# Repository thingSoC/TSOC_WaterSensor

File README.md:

# TSOC_WaterSensor - Passive Water Sensor Module :

The TSOC_WaterSensor is a simple passive water sensor with Grove Connectors, 
in an Embedded Module format for the new thingSoC, Internet of Things open standard.
It includes a secondl breakout connector for an additional sensor (Temperature/Humidity) or actuator (Relay/Mosfet).
It is designed to be used as a basement/sump water detector that engages a pump or alarm when water is present.
The addiitional connector can be used to add a humidity/temperature sensor (ie. basement too hot or too moist),
or for a an actuator, like a Relay (to turn on the sump pump when water is detected, etc.).

The TSOC_WaterSensor is a low cost, embeddable module featuring :

* Simple, Passive Water Sensor
* Additional Breakout connector
* Mounting holes
* [thingSoC Compliant Module](http://www.thingsoc.com)
* [Mikrobus Compatible Module](http://www.mikroe.com/mikrobus/) 

[TSOC_WaterSensor](https://github.com/thingSoC/TSOC_WaterSensor)

**thingSoC Reference Designs** are example thingSoC implementations that implement
various reference and testing circuits for demonstrating the use of the thingSoC libraries.
These reference designs can serve as starting templates for user designs.

---------------------------------------

## TSOC_WaterSensor Instructions

The TSOC_WaterSensor can use either digital or analog inputs for water detection.
The additional breakout connector can be used for an additional sensor (Temperature/Humidity) or actuator (Relay/Mosfet).

---------------------------------------

## TSOC_WaterSensor Status <a name="TSOC_WaterSensor_status"/>

**11/06/2016:** 
Revision 1.0 - Initial Layout released to OSHpark

---------------------------------------
## TSOC_WaterSensor Model Images

[TSOC_WaterSensor](https://github.com/thingSoC/TSOC_WaterSensor)

[TSOC_WaterSensor](https://github.com/thingSoC/TSOC_WaterSensor)

---------------------------------------

## TSOC_WaterSensor Documentation Index <a name="TSOC_WaterSensor_documentation_index"/>

[TSOC_WaterSensor Project](http://thingsoc.github.io/projects/TSOC_WaterSensor.html)

[TSOC_WaterSensor Hardware](https://github.com/thingSoC/TSOC_WaterSensor/tree/master/TSOC_WaterSensor/hardware)

---------------------------------------

## thingSoC Documentation Index <a name="thingSoC_documentation_index"/>

[thingSoC Organization Website](http://thingSoC.github.io)

[thingSoC FAQ - Frequently Asked Questions](http://thingsoc.github.io/support/faq.html)

---------------------------------------

[ 
*thingSoC*](http://thingsoc.github.io)

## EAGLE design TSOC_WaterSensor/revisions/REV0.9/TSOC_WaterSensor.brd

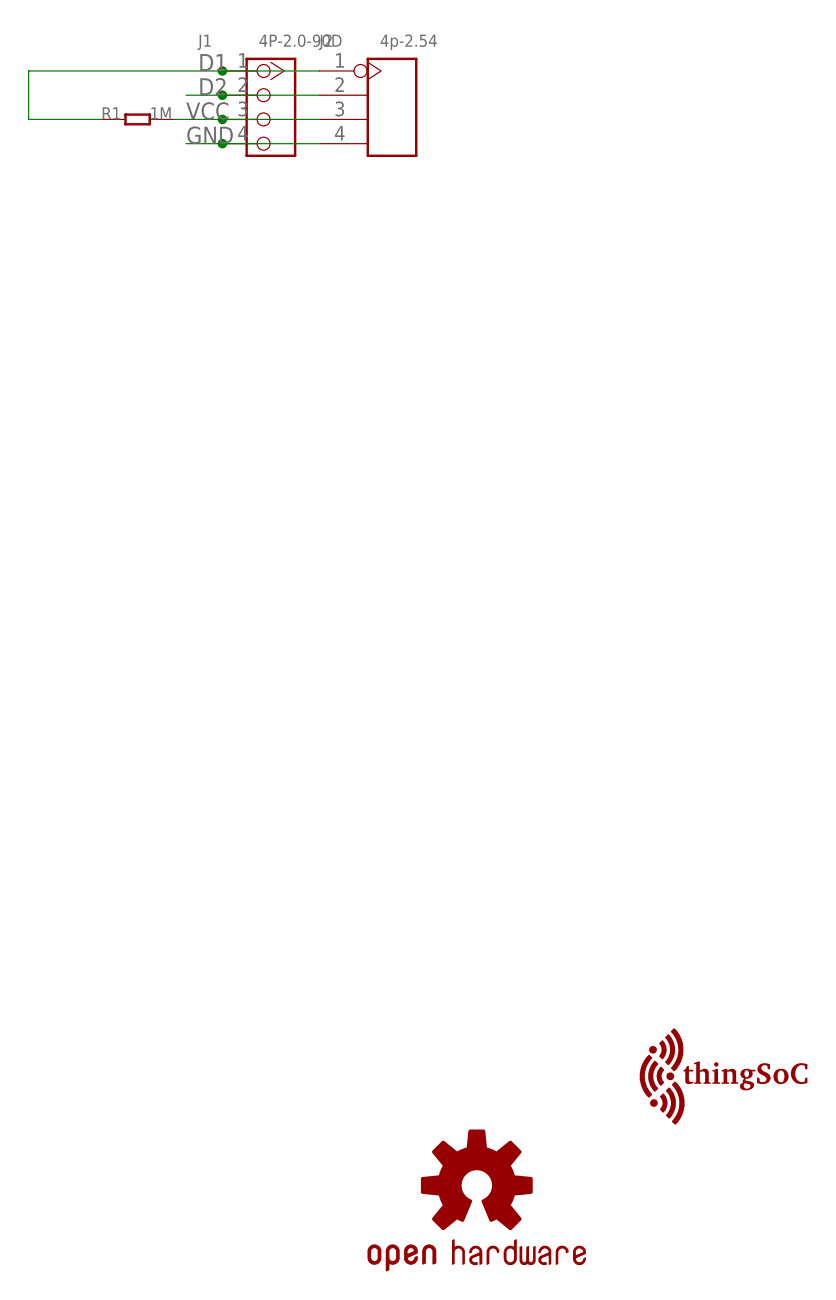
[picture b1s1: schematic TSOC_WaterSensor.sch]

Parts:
J1: 4P-2.0-90D; HW4-2.0-90D
J2: 4p-2.54; H4-2.54
R1: 1M; 0603
U$1: OSHW_LOGO_SYMM; OSHW_LOGO_MED_SYM
U$2: TSOC-LOGO-LRG

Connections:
D1: J1.1, J2.1, R1.1
D2: J1.2, J2.2
GND: J1.4, J2.4
VCC: J1.3, J2.3, R1.2

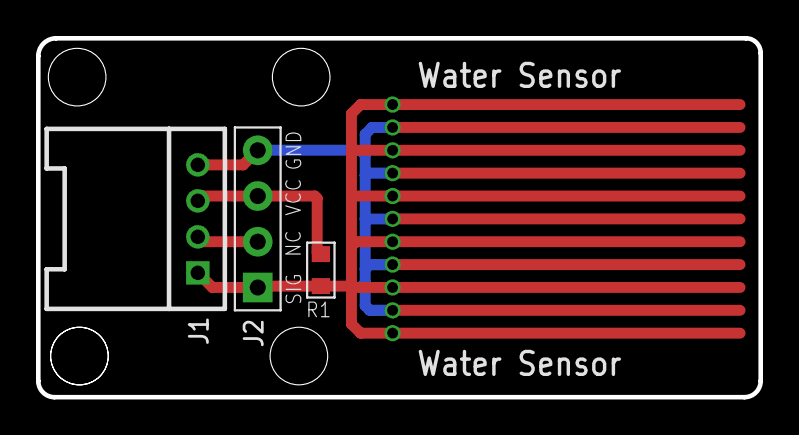
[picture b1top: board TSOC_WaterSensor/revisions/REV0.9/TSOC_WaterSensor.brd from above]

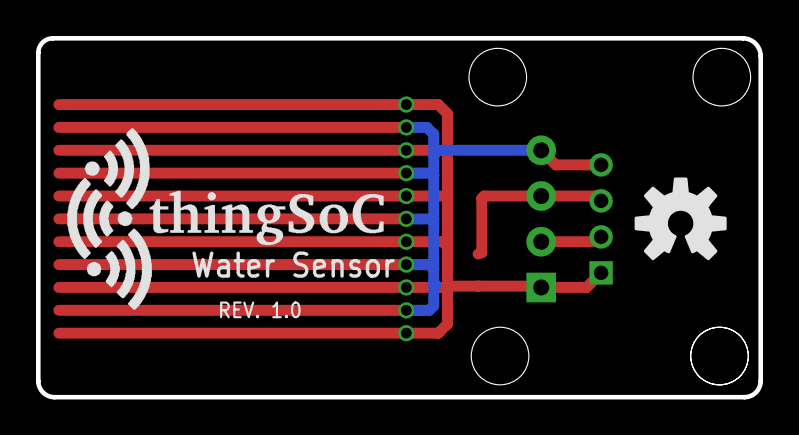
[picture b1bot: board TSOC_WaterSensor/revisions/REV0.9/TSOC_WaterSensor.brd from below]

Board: 2 copper layers, 40.1 x 19.9 mm, 5 parts (2 on the bottom side), 4 nets.

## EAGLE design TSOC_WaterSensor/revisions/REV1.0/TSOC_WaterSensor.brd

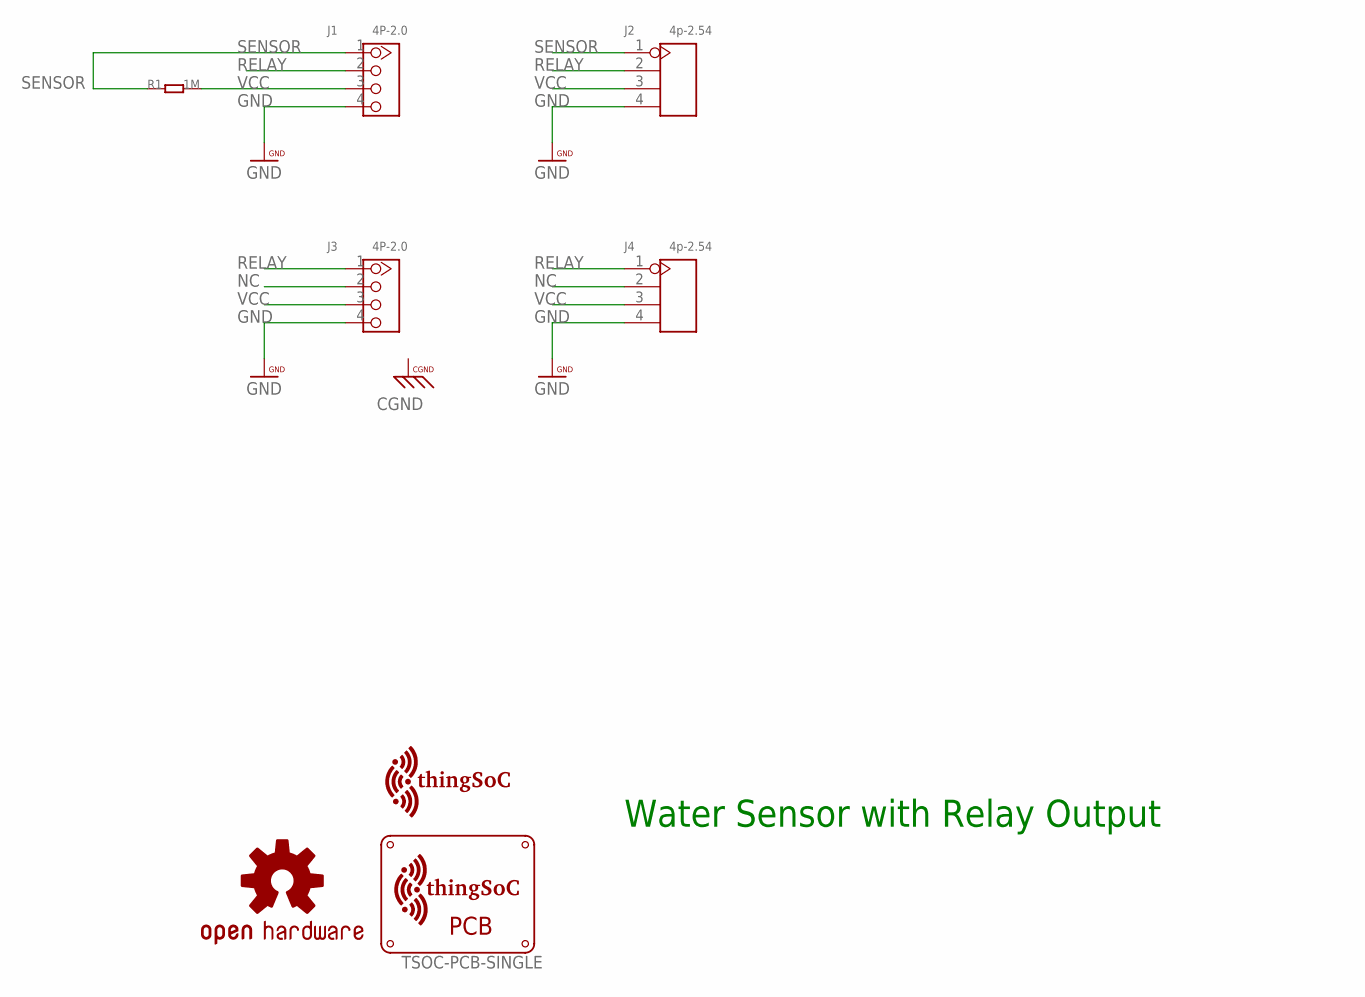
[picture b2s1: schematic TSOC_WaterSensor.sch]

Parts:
J1, J3: 4P-2.0; HW4-2.0
J2, J4: 4p-2.54; H4-2.54
R1: 1M; 0603
U$1: OSHW_LOGO_SYMM; OSHW_LOGO_MED_SYM
U$2: TSOC-LOGO-LRG
U$3: TSOC-PCB-SINGLE; TSOC-BB-BRD-DIM

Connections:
GND: J1.4, J2.4, J3.4, J4.4
NC: J3.2, J4.2
RELAY: J1.2, J2.2, J3.1, J4.1
SENSOR: J1.1, J2.1, R1.1
VCC: J1.3, J2.3, J3.3, J4.3, R1.2

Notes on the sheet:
Water Sensor with Relay Output

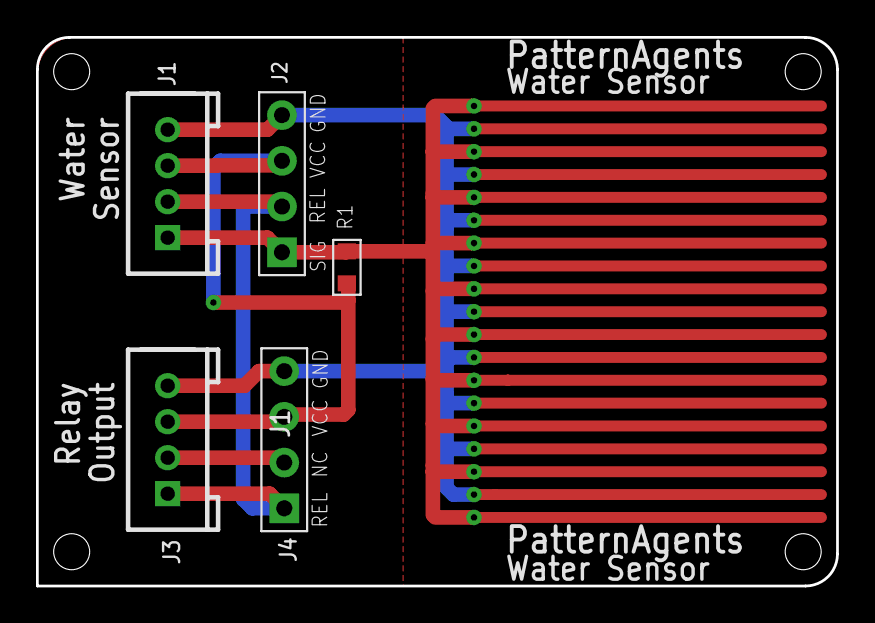
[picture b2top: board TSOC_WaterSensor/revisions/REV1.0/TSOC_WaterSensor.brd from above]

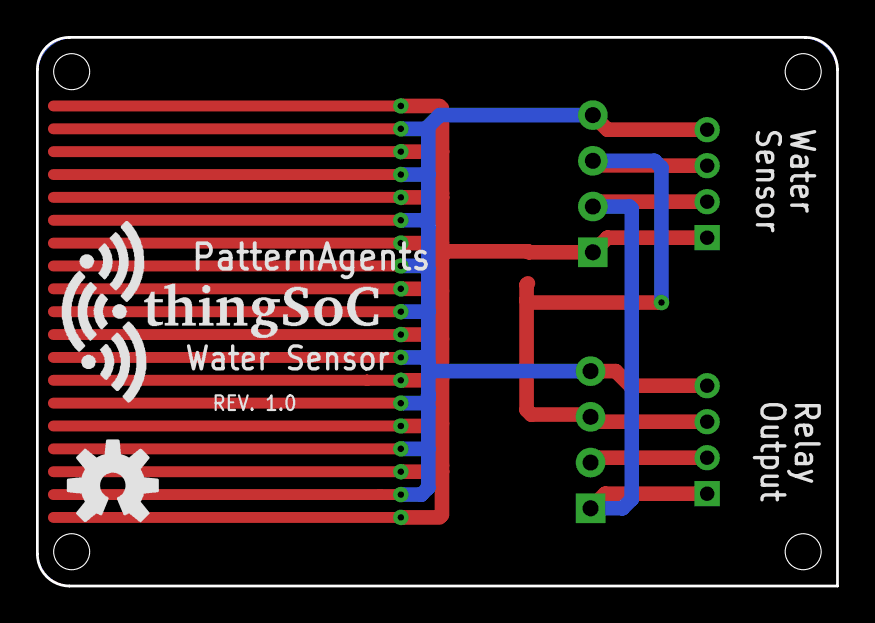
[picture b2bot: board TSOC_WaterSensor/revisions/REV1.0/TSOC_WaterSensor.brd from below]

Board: 2 copper layers, 44.5 x 30.5 mm, 8 parts (2 on the bottom side), 5 nets.

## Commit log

2017-01-18 update documentation
2017-01-18 update examples

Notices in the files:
parts and their libraries:
PatternAgents-Logos: License : http://creativecommons.org/licenses/by-sa/3.0
(Creative Commons 3.0)
thingSoC: License : http://creativecommons.org/licenses/by-sa/4.0
(Creative Commons 4.0)
